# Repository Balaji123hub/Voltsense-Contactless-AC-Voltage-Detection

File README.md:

# Voltsense – Contactless AC Voltage Detection PCB

## Overview

Voltsense is a custom PCB designed for a contactless AC voltage detection system. The board integrates the sensing circuit, signal conditioning, indicator LEDs, buzzer interface, and power supply into a compact and reliable design suitable for embedded and electrical applications.

---

## Features

- Contactless AC voltage detection
- Compact 2-layer PCB design
- LED indication
- Buzzer output
- Optimized component placement
- Clean PCB routing
- Design Rule Check (DRC) verified
- Manufacturing-ready Gerber generation

---

## Tools Used

- KiCad
- PCB Layout Editor
- Design Rule Check (DRC)
- Gerber File Generation

---

## Design Specifications

| Parameter | Value |
|-----------|-------|
| Board Type | 2-Layer PCB |
| Application | Contactless AC Voltage Detection |
| Design Software | Autodesk Fusion 360 |
| Status | Completed |

---

# Project Images

## Schematic Diagram

---

## PCB Render

---

## Top View

---

## Bottom View

---

## 3D View

---

## Design Process

- Circuit schematic design
- Component selection
- PCB footprint assignment
- Component placement
- PCB routing
- Design Rule Check (DRC)
- 3D verification
- Gerber file generation

---

## Skills Demonstrated

- PCB Design
- Schematic Capture
- PCB Routing
- Electronic Hardware Design
- DRC Verification
- Gerber Generation
- Embedded Hardware Development

---

## Future Improvements

- EMI/EMC optimization
- PCB miniaturization
- Reverse polarity protection
- Over-voltage protection
- Hardware testing and validation

---

## Author

**Balaji M**

Electrical and Electronics Engineering

Interested in Embedded Systems, PCB Design, IoT, Smart Grid, and Hardware Product Development.

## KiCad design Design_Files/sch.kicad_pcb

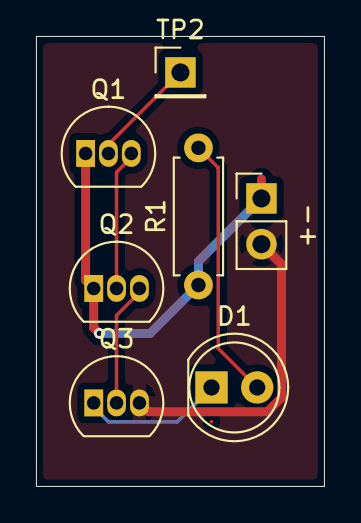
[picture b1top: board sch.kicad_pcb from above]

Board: 2 copper layers, 16.0 x 25.0 mm, 7 parts (0 on the bottom side), 7 nets.

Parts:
+-: BATTERY; PinHeader_1x02_P2.54mm_Vertical
D1: LED; LED_D5.0mm
Q1, Q2, Q3: BC547; TO-92_Inline
R1: 110; R_Axial_DIN0207_L6.3mm_D2.5mm_P7.62mm_Horizontal
TP2: TestPoint; PinHeader_1x01_P2.54mm_Vertical

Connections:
GND: +-.2, Q3.3 (E)
unnamed: D1.2 (A), R1.2
unnamed: D1.1 (K), Q3.1 (C)
unnamed: Q1.2 (B), TP2.1 (1_1)
unnamed: Q1.3 (E), Q2.2 (B)
unnamed: Q2.3 (E), Q3.2 (B)
VCC: +-.1, Q1.1 (C), Q2.1 (C), R1.1
